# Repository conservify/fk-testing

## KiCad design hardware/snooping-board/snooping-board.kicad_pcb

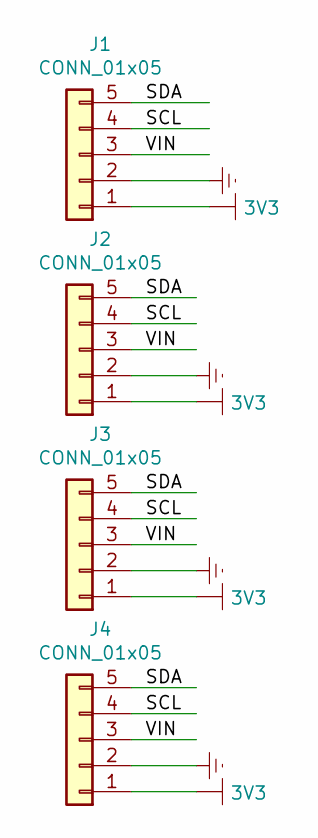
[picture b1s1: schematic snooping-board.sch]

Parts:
J1, J2: CONN_01x05; Molex_CLIK-Mate_502382-0570_1x05_P1.25mm_Vertical
J3, J4: CONN_01x05; Socket_Strip_Straight_1x05_Pitch2.54mm

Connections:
3V3: J1.1, J2.1, J3.1, J4.1
/SCL: J1.4, J2.4, J3.4, J4.4
/SDA: J1.5, J2.5, J3.5, J4.5
/VIN: J1.3, J2.3, J3.3, J4.3
GND: J1.2, J2.2, J3.2, J4.2

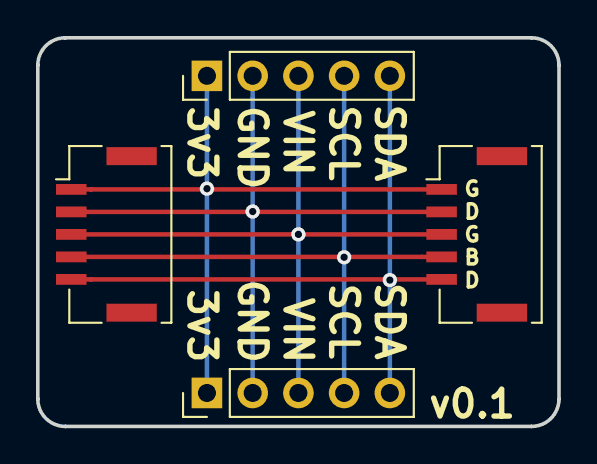
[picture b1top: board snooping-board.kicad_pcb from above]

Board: 2 copper layers, 29.0 x 21.6 mm, 4 parts (0 on the bottom side), 5 nets.

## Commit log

2018-01-09 LAN Sync tool this listens for devices on the network and downloads.
2018-01-09 Preparing to slurp downloaded logs through some analysis.
2018-01-12 Add a tool to dump DATA.BIN files.
2018-01-16 Include timestamp in written files.
2018-01-18 use protocol buffers to decode readings file.
2018-02-05 Some random refactoring. Clean up logging and the data.
2018-02-05 Adding some monitoring/test scripts we use on the weather pi.
2018-02-05 Fix race/concurrency issue with the bytes buffer.
2018-02-07 Use new download call.
2018-02-07 Parse sensor readings and GPS fixes from text logs.
2018-02-07 Hacked together code to pull data from a FK data file and upload.
2018-02-07 Directory rename.
2018-02-09 Skip "unfixed" readings, for now.
2018-02-13 Install targets.
2018-02-14 Wifi tool for interacting with Core over its own AP.
2018-02-14 Some testing scripts for the weather monitoring Pi.
2018-02-14 More test scripts.
2018-02-14 Adding DataDirectory parameter.
2018-02-14 Pass interface to wpa_cli
2018-02-14 Use a non standard control socket so we can play nice.
2018-02-14 Bare bones script to upload binary.
2018-02-14 Data tool can upload to the streaming endpoint now.
    We also solve the metadata problem by keep the last metadata record saw
    saved in the directory.
2018-02-15 Hack to chown data files we write.
2018-02-15 Use unique AP name for my test device.
2018-02-16 Enable a mode where we let the OS deal with the wifi we just scan.
2018-02-19 Improving the test platform maintenance scripts.
2018-02-21 Use flash scripts that lock out the tailing remotely.
2018-02-26 Move writer code into separate files. Break deps.
2018-02-26 Writer stuff is in utilities package now.
2018-02-26 Wifi tool can also upload data files now.
2018-02-26 Moving scripts to bin dir.
2018-02-27 Using sudo to run flasher and wifi-tool. No more setuid.
2018-02-28 Don't die when we can't upload the file. Try 3 times.
2018-03-02 Always write the record to the server.
    Fixes a bug where even though we'd see an updated metadata we'd skip
    writing that to the buffer. So when a file had metadata we'd never send
    and only send when we had to use cached metadata.
2018-03-07 Ignore meta records in CSV writer.
2018-03-09 Pass known weather Wifi AP name to wifi tool
2018-03-09 Wifi tool errors and also only scan if we don't know the network.
2018-03-09 Create nested directories by year-month and day.
2018-03-14 Simple analyse script.
2018-03-14 Build fix from the JSON upgrade.
2018-03-14 Ignore metadata w/o sensors.
2018-03-14 Fix go dependencies.
2018-03-15 Lots of data-tool features.
    Can split files. Force device ids. Flexible transformation pipeline/chain.
2018-03-15 Append last metadata to beginning of new batch files.
2018-03-15 Ignore *.fkpb
2018-03-15 Ensure proper networking configuration in test flashes.
2018-03-19 When spitting we weren't writing the encoded bytes.
2018-03-20 Data tool is much more flexible now. Less destructive.
2018-03-21 Echo response content when streaming.
2018-03-22 Wipe card helper. Also fix hostnames in atlas-pi-upgrade
2018-03-23 Package changes from backend refactor.
2018-03-23 Configuration to tell stream writer to set async flag.
2018-03-27 Export structured log from a binary file.
2018-05-03 Always build arm and amd64 binaries.
2018-05-03 A friendlier multi-arch build.
2018-05-03 Log position in the stream for debugging when verbose.
2018-05-04 Disable radio on Atlas/Weather test stations.
2018-05-07 Log position on parse errors.
2018-05-15 Bounce errors up to main.
2018-05-16 Add test row for our other fknat.
2018-05-18 Break FileWriter into a file and allow for writing numbered files.
2018-05-18 Flag to write to a file.
2018-05-22 Add another test device.
2018-05-22 Install would have overwritten.
2018-05-23 Keep wifi on for our test instances.
    This is mostly for the weather since we don't create an AP more than once.
2018-05-23 Add an interval to wifi tool.
    Otherwise always on wifi mode never yields a connect/disconnect change.
2018-05-23 Upload all files. Also only upload once, bug was uploading 3 times.
2018-06-27 Build osx stuff, fix call to DownloadFileToWriter.
2018-07-05 Fix pi upgrade scripts after build path changes.
2018-07-05 Download entire files.
2018-07-09 Compile flags for test stations.
2018-07-11 Set compile flags to mimic Amazon deploy.
2018-07-11 Pull env variables out of setup script.
2018-07-12 Pass empty flags for now.
2018-07-12 Update testing scripts now that Wifi works on our test weather.
2018-07-14 Migrating to FK prefixed options
2018-07-19 Query status. Flag to control downloading files.
2018-07-19 Notify every few minutes.
2018-07-31 Configs for our test stations. These need to be upgraded.
2018-07-31 Fix binary name.
2018-08-02 Set processing flag no matter what. Pass UploadName header.
2018-08-03 Add Jenkinsfile.
2018-08-08 Use Wire11and13 on atlas test station for now.
2018-08-09 Use conservifyProperties.
2018-08-28 Fix path to binaries.
2018-10-19 Option to format times in CSV output.
2018-11-08 Add option to disable querying, just monitoring.
2018-11-08 Seconds for intervals and use a shorter one for querying.
2018-11-08 Make the use of notify-send configurable.
2018-12-04 Throwing together a quick snooping board.
2019-02-15 Makefile parallel fixes.
2019-02-28 Fix position logging off by length of message size bytes.
2019-04-10 Add some logging and some quick docs.
2019-04-10 Ability to restart background processes. Watch tcpdump.
2019-04-10 Query the device status.
2019-04-16 Fix logging of position, include size of message with prefix.
2019-04-23 Use absolute BUILD in Makefile.
2019-05-02 Log byte size information when parsing file.
2019-05-06 Add log level to log output.
2019-05-06 Include wall clock time when dumping logs.
2019-05-30 Move to new golang modules.
2019-10-22 Target to update protobuf packages.
2019-10-22 Hack things to build again. Been a long time.
2019-11-02 Some simple tests.
2023-02-15 Bump github.com/prometheus/client_golang from 1.2.1 to 1.11.1
    Bumps [github.com/prometheus/client_golang](https://github.com/prometheus/client_golang) from 1.2.1 to 1.11.1.
    - [Release notes](https://github.com/prometheus/client_golang/releases)
    - [Changelog](https://github.com/prometheus/client_golang/blob/main/CHANGELOG.md)
    - [Commits](https://github.com/prometheus/client_golang/compare/v1.2.1...v1.11.1)
    ---
    updated-dependencies:
2023-02-24 Bump golang.org/x/net from 0.0.0-20191021144547-ec77196f6094 to 0.7.0
    Bumps [golang.org/x/net](https://github.com/golang/net) from 0.0.0-20191021144547-ec77196f6094 to 0.7.0.
    - [Release notes](https://github.com/golang/net/releases)
    - [Commits](https://github.com/golang/net/commits/v0.7.0)
    ---
    updated-dependencies:
    - dependency-name: golang.org/x/net
2023-02-25 Bump golang.org/x/crypto from 0.0.0-20191011191535-87dc89f01550 to 0.1.0
    Bumps [golang.org/x/crypto](https://github.com/golang/crypto) from 0.0.0-20191011191535-87dc89f01550 to 0.1.0.
    - [Release notes](https://github.com/golang/crypto/releases)
    - [Commits](https://github.com/golang/crypto/commits/v0.1.0)
    ---
    updated-dependencies:
    - dependency-name: golang.org/x/crypto
2023-02-25 Bump golang.org/x/sys from 0.0.0-20191022100944-742c48ecaeb7 to 0.1.0
    Bumps [golang.org/x/sys](https://github.com/golang/sys) from 0.0.0-20191022100944-742c48ecaeb7 to 0.1.0.
    - [Release notes](https://github.com/golang/sys/releases)
    - [Commits](https://github.com/golang/sys/commits/v0.1.0)
    ---
    updated-dependencies:
    - dependency-name: golang.org/x/sys
